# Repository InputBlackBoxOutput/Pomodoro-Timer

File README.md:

# Pomodoro Timer

A Pomodoro timer helps you focus on a task for 25 minutes and then take a 5-minute break

## 5 steps of the Pomodoro technique
1. Choose a task
2. Set the timer for 25 minutes
3. Work on the task until the timer rings
4. Take a 5-minute break
5. Repeat steps 1-4 three more times

## 3D Render: PCB + Enclosure

## Hardware block diagram

| Component | Function |
|--|--|
| ATmega328P            | Micro-controller that controls all functionality                  |
| LED                   | Indicate the status of the Pomodoro timer                         |
| Push buttons          | Provide an interface to start/stop and reset the Pomodoro timer   |
| Buzzer                | Provide auditory feedback upon completion of the timer            |
| 4x7 segment display   | Displays remaining time for the Pomodoro session                  |
| LDO voltage regulator | Efficiently regulates the voltage supplied to the embedded system |
| Cell battery          | Provides power to the entire system                               |

### Made with lots of ⏱️, 📚 and ☕ by InputBlackBoxOutput

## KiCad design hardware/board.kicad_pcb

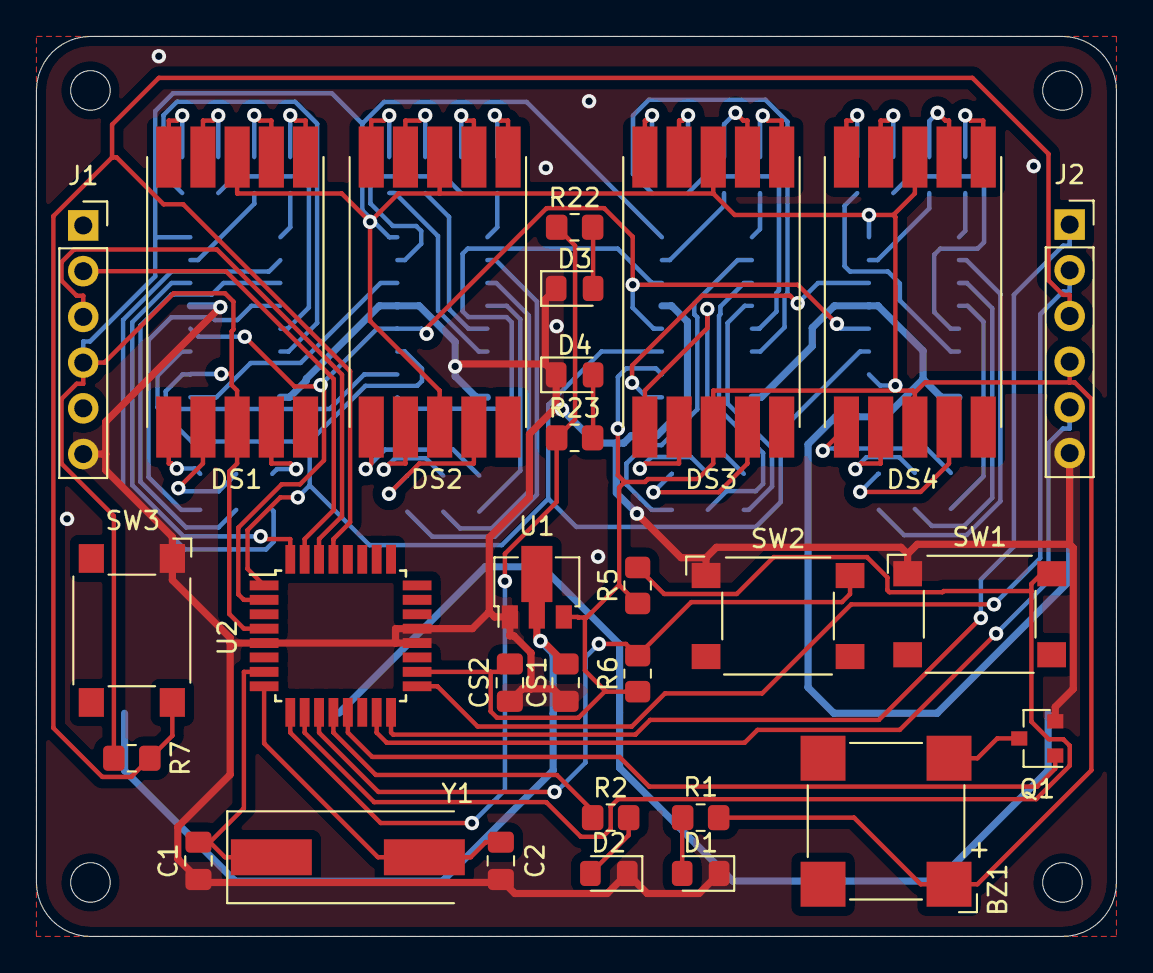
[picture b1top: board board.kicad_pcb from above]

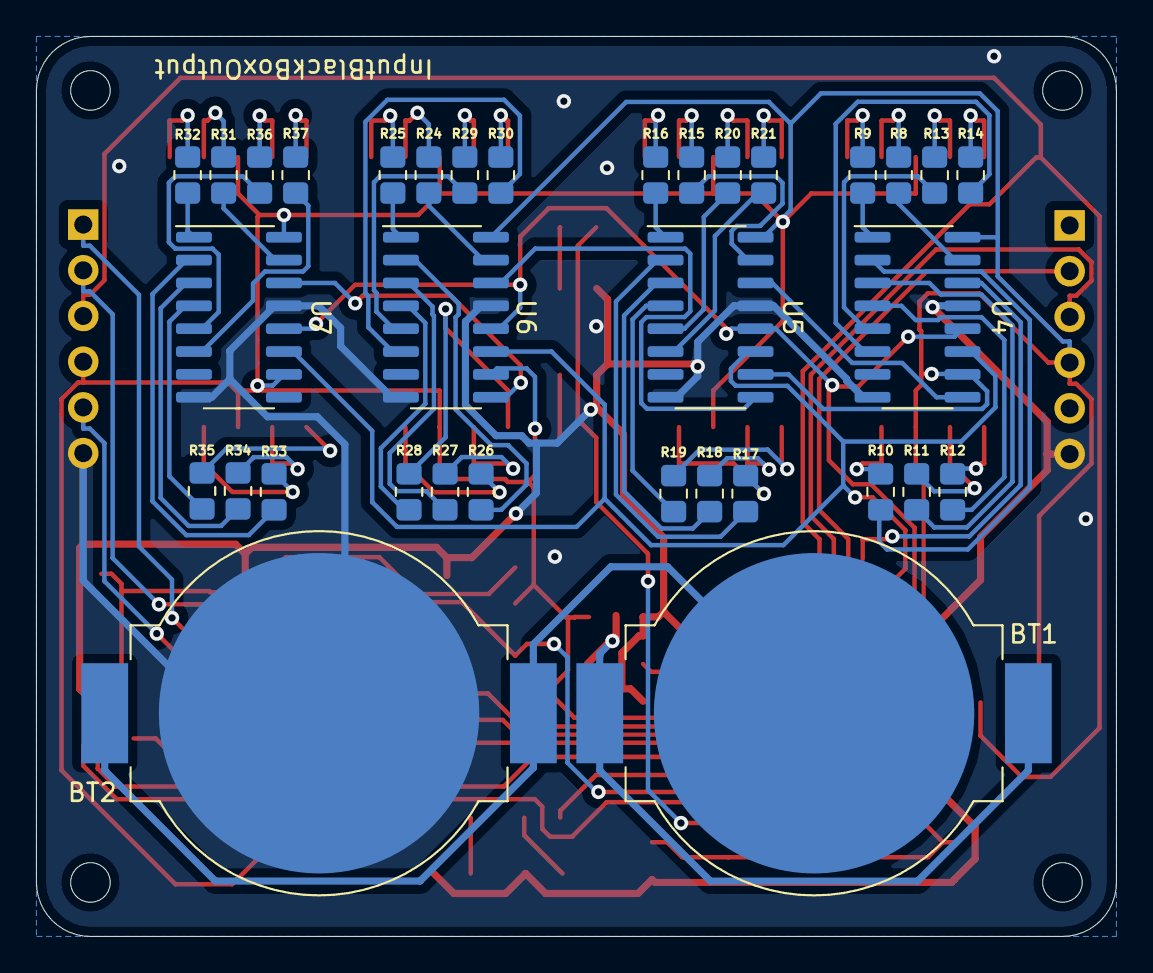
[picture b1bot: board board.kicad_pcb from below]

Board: 2 copper layers, 60.0 x 50.0 mm, 67 parts (34 on the bottom side), 84 nets.

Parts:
BT1, BT2: Battery_Cell; BatteryHolder_MPD_BC2003_1x2032
BZ1: Buzzer; MagneticBuzzer_CUI_CMT-8504-100-SMT
C1, C2: 22pF; C_0805_2012Metric_Pad1.18x1.45mm_HandSolder
CS1: 10uF; C_0805_2012Metric_Pad1.18x1.45mm_HandSolder
CS2: 22uF; C_0805_2012Metric_Pad1.18x1.45mm_HandSolder
D1, D2, D3, D4: LED; LED_0805_2012Metric_Pad1.15x1.40mm_HandSolder
DS1, DS2, DS3, DS4: ELSS-406SURWA
H1, H2, H3, H4: MountingHole; MountingHole_2.2mm_M2
J1, J2: Conn_01x06_Female; PinSocket_1x06_P2.54mm_Vertical
Q1: AO3400A; SOT-23
R1, R2, R22, R23: 2.2k; R_0805_2012Metric_Pad1.20x1.40mm_HandSolder
R5, R6: 10k; R_0805_2012Metric_Pad1.20x1.40mm_HandSolder
R7: 10K; R_0805_2012Metric_Pad1.20x1.40mm_HandSolder
R8, R9, R10, R11, R12, R13, R14, R15, R16, R17, R18, R19, R20, R21, R24, R25, R26, R27, R28, R29, R30, R31, R32, R33, R34, R35, R36, R37: 220R; R_0805_2012Metric_Pad1.20x1.40mm_HandSolder
SW1: BTN1; SW_SPST_Omron_B3FS-100xP
SW2: BTN2; SW_SPST_Omron_B3FS-100xP
SW3: BTN3; SW_SPST_Omron_B3FS-100xP
U1: HT7833-1-SOT89; SOT-89-3
U2: ATmega328PB-AU; TQFP-32_7x7mm_P0.8mm
U4, U5, U6, U7: 74HC595; SOP-16_3.9x9.9mm_P1.27mm
Y1: 8MHz; Crystal_SMD_HC49-SD

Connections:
+3V3: BZ1.1, CS2.1, DS1.3, DS1.8, DS2.3, DS2.8, DS3.3, DS3.8, DS4.3, DS4.8, J1.4, J2.4, R1.1, R5.1, R6.1, R7.1, U1.3, U2.4, U2.18, U4.10, U4.16, U5.10, U5.16, U6.10, U6.16, U7.10, U7.16
+BATT: BT1.1, CS1.1, U1.2
/BTN_1: R5.2, SW1.2, U2.10
/BTN_2: R6.2, SW2.2, U2.11
/BUZZER: Q1.1, U2.13
/Display/1_OUT: U4.9, U5.14
/Display/2_OUT: U5.9, U6.14
/Display/3_OUT: U6.9, U7.14
/LED: R2.1, U2.12
/MISO: J2.1, U2.16
/MOSI: J2.5, U2.15
/RESET: J2.3, R7.2, SW3.2, U2.29
/RX: J1.3, U2.30
/SCK: J2.2, U2.17
/TX: J1.2, U2.31
/XTAL_1: C1.2, U2.7, Y1.1
/XTAL_2: C2.2, U2.8, Y1.2
GND: BT2.2, C1.1, C2.1, CS1.2, CS2.2, D1.1, D2.1, D3.1, D4.1, J1.6, J2.6, Q1.2, SW1.1, SW2.1, SW3.1, U1.1, U2.5, U2.20, U2.21, U4.8, U4.13, U5.8, U5.13, U6.8, U6.13, U7.8, U7.13
LATCH: U2.2, U4.12, U5.12, U6.12, U7.12
LED:: R22.1, R23.1, U2.9
unnamed: BT1.2, BT2.1
unnamed: BZ1.2, Q1.3
unnamed: D1.2, R1.2
unnamed: D2.2, R2.2
unnamed: D3.2, R22.2
unnamed: D4.2, R23.2
unnamed: DS1.1, R12.1
unnamed: DS1.2, R11.1
unnamed: DS1.4, R10.1
unnamed: DS1.6, R9.1
unnamed: DS1.7, R8.1
unnamed: DS1.9, R13.1
unnamed: DS1.10, R14.1
unnamed: DS2.1, R19.1
unnamed: DS2.2, R18.1
unnamed: DS2.4, R17.1
unnamed: DS2.6, R16.1
unnamed: DS2.7, R15.1
unnamed: DS2.9, R20.1
unnamed: DS2.10, R21.1
unnamed: DS3.1, R28.1
unnamed: DS3.2, R27.1
unnamed: DS3.4, R26.1
unnamed: DS3.6, R25.1
unnamed: DS3.7, R24.1
unnamed: DS3.9, R29.1
unnamed: DS3.10, R30.1
unnamed: DS4.1, R35.1
unnamed: DS4.2, R34.1
unnamed: DS4.4, R33.1
unnamed: DS4.6, R32.1
unnamed: DS4.7, R31.1
unnamed: DS4.9, R36.1
unnamed: DS4.10, R37.1
unnamed: R8.2, U4.15
unnamed: R9.2, U4.1
unnamed: R10.2, U4.2
unnamed: R11.2, U4.3
unnamed: R12.2, U4.4
unnamed: R13.2, U4.5
unnamed: R14.2, U4.6
unnamed: R15.2, U5.15
unnamed: R16.2, U5.1
unnamed: R17.2, U5.2
unnamed: R18.2, U5.3
unnamed: R19.2, U5.4
unnamed: R20.2, U5.5
unnamed: R21.2, U5.6
unnamed: R24.2, U6.15
unnamed: R25.2, U6.1
unnamed: R26.2, U6.2
unnamed: R27.2, U6.3
unnamed: R28.2, U6.4
unnamed: R29.2, U6.5
unnamed: R30.2, U6.6
unnamed: R31.2, U7.15
unnamed: R32.2, U7.1
unnamed: R33.2, U7.2
unnamed: R34.2, U7.3
unnamed: R35.2, U7.4
unnamed: R36.2, U7.5
unnamed: R37.2, U7.6
SERIAL_CLOCK: U2.1, U4.11, U5.11, U6.11, U7.11
SERIAL_DATA: U2.32, U4.14

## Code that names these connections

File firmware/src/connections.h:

#ifndef CONNECTIONS_H
#define CONNECTIONS_H

    #define LED           8
    #define BUZZER        9
    
    #define BTN1          6
    #define BTN2          7
    
    #define SERIAL_DATA   2
    #define SERIAL_CLK    3
    #define LATCH         4
    #define LED_COLON     5

#endif

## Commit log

2022-02-15 Hardware added
2022-02-15 Enclosure added
2022-02-24 Firmware added
2022-02-24 Images added
2022-02-28 README: Image added
2022-07-03 Folder reorganized: hardware
2022-10-26 Directory created: docs + Datasheets added
2022-10-26 README: Hardware block diagram added
2023-09-30 README: Info added
